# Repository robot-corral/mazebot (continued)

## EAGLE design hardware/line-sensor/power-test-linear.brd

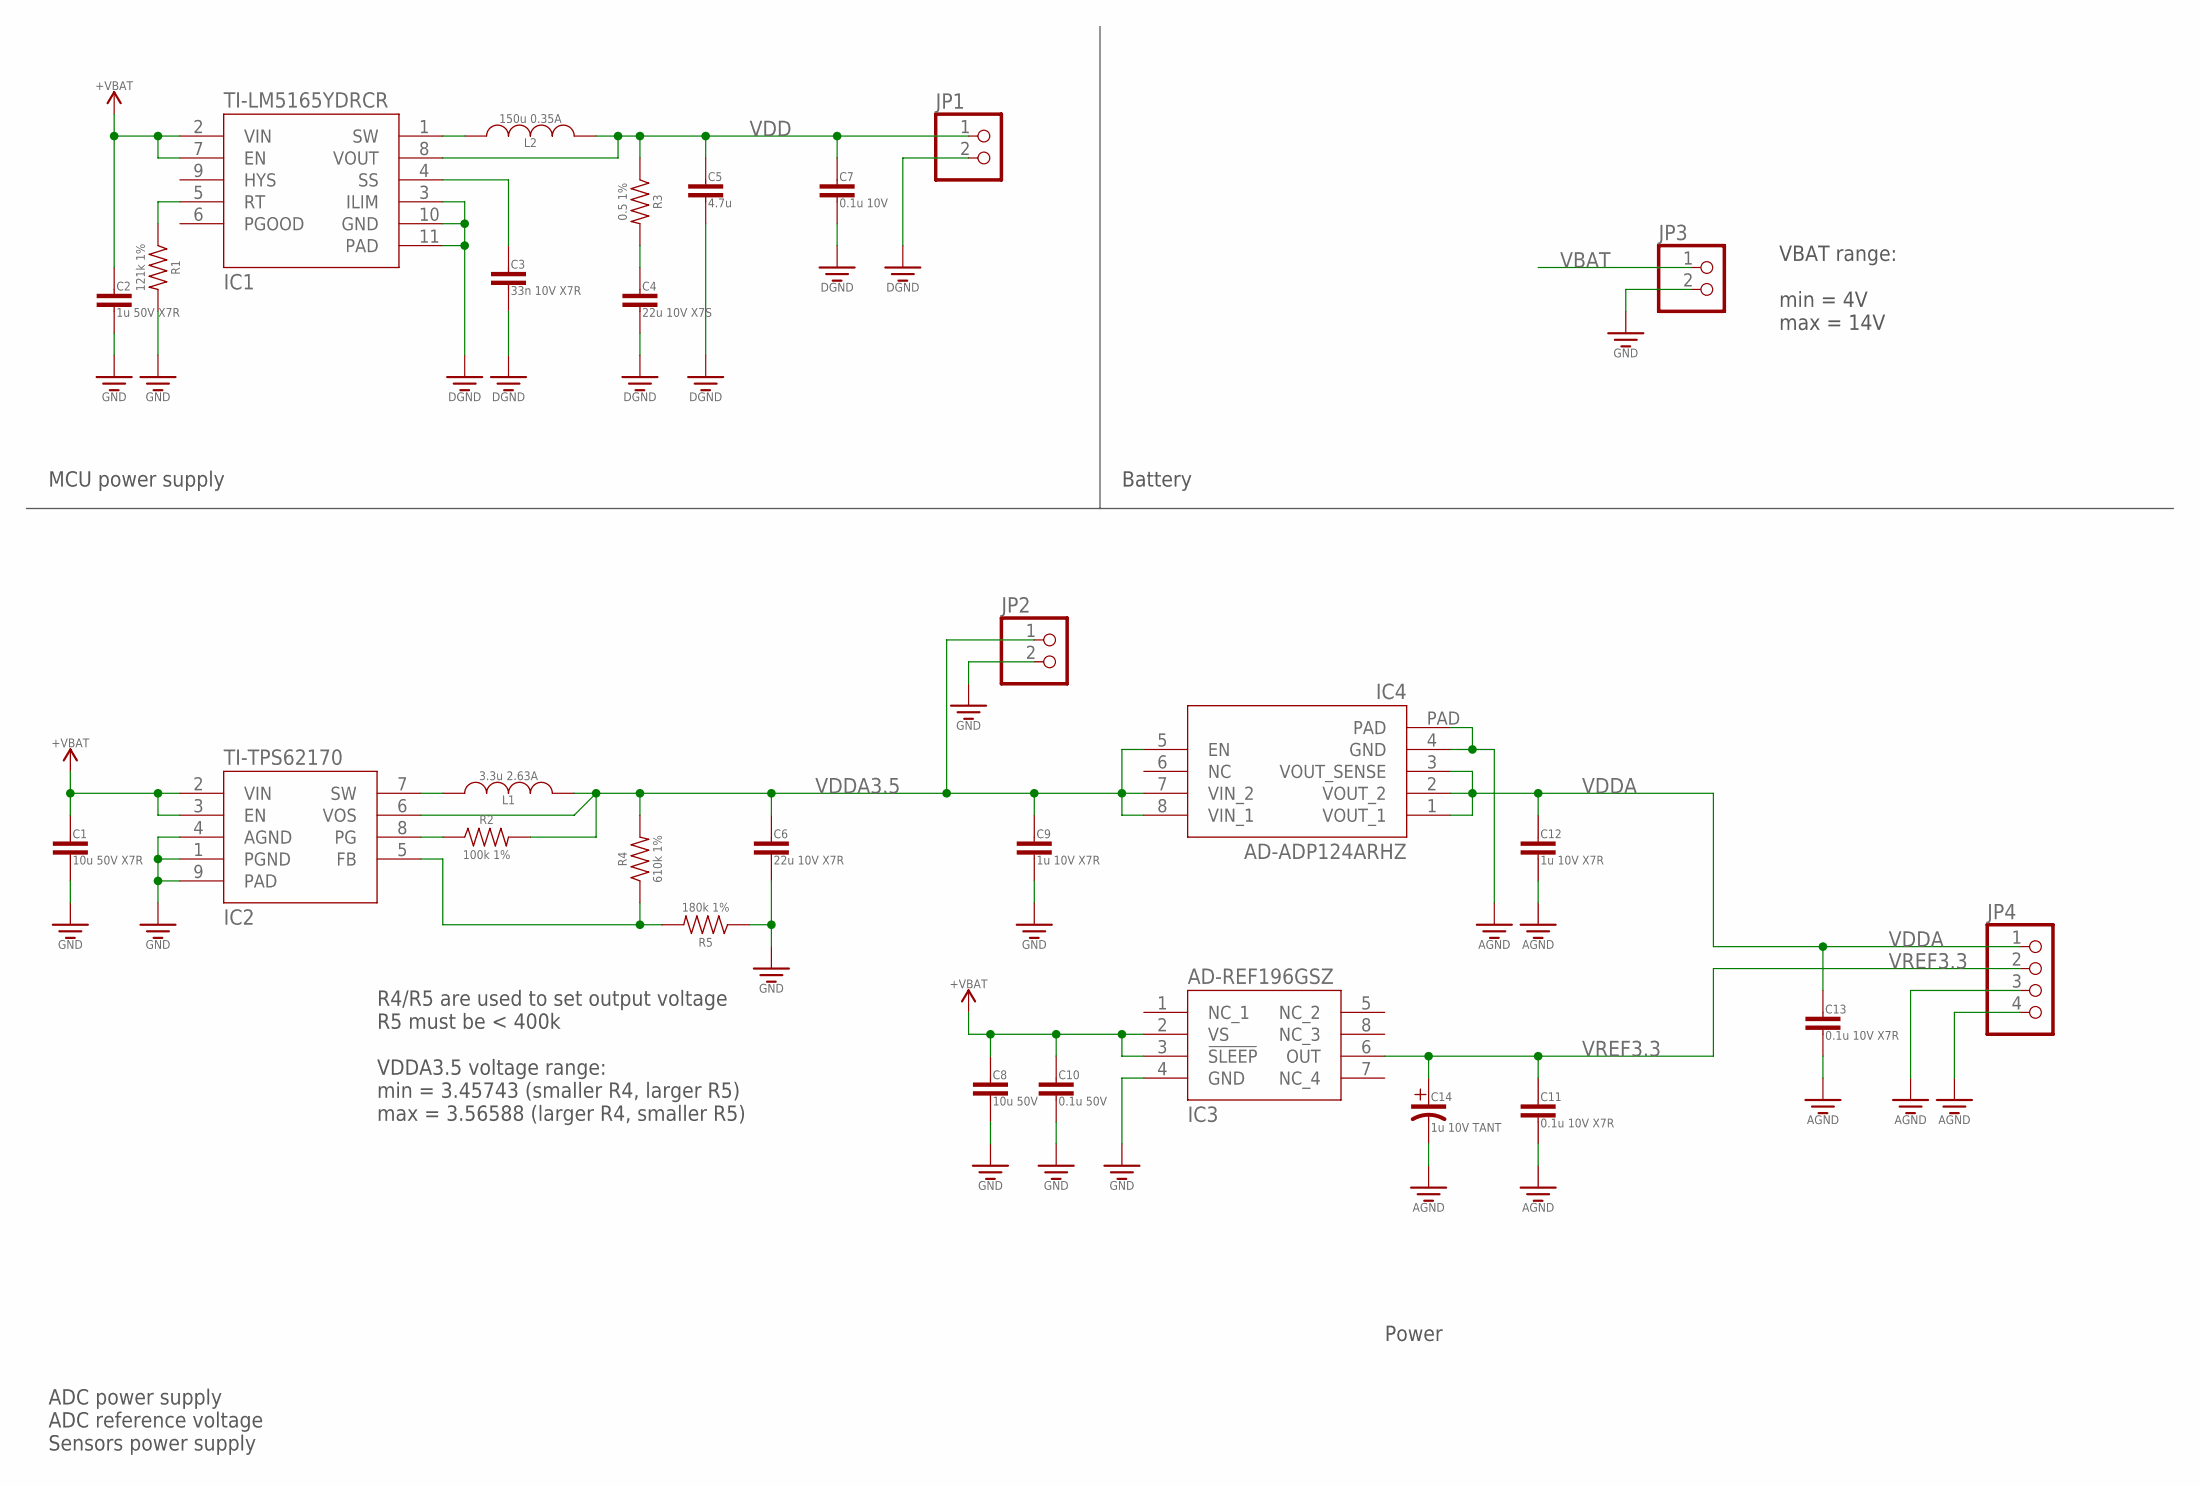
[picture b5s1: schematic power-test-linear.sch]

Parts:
C1: 10u 50V X7R; CAPACITOR-0805
C2: 1u 50V X7R; CAPACITOR-1206
C3: 33n 10V X7R; CAPACITOR-0603
C4: 22u 10V X7S; CAPACITOR-0805
C5: 4.7u; CAPACITOR-0805
C6: 22u 10V X7R; CAPACITOR-0805
C7: 0.1u 10V; CAPACITOR-0805
C8: 10u 50V; CAPACITOR-0805
C9, C12: 1u 10V X7R; CAPACITOR-0805
C10: 0.1u 50V; CAPACITOR-0805
C11, C13: 0.1u 10V X7R; CAPACITOR-0805
C14: 1u 10V TANT; CAPACITOR_POLARIZED-1411-(3528-MET)
IC1: TI-LM5165YDRCR; VSON-10-0.5MM
IC2: TI-TPS62170; WSON-8-0.5MM
IC3: AD-REF196GSZ; SOIC-8
IC4: AD-ADP124ARHZ; MSOP-8-EP
JP1, JP2, JP3: PINHD-1X2; 1X02
JP4: PINHD-1X4; 1X04
L1: 3.3u 2.63A; VLS3012HBX
L2: 150u 0.35A; ELL-6SH151M
R1: 121k 1%; RESISTOR-0603
R2: 100k 1%; RESISTOR-0603
R3: 0.5 1%; RESISTOR-0603
R4: 610k 1%; RESISTOR-0603
R5: 180k 1%; RESISTOR-0603

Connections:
AGND: C11.2, C12.2, C13.2, C14.NEG, IC4.4 (GND), IC4.PAD, JP4.3, JP4.4
DGND: C3.2, C4.2, C5.2, C7.2, IC1.3 (ILIM), IC1.10 (GND), IC1.11 (PAD), JP1.2
GND: C1.2, C2.P$2 (2), C6.2, C8.2, C9.2, C10.2, IC2.1 (PGND), IC2.4 (AGND), IC2.9 (PAD), IC3.4 (GND), JP2.2, JP3.2, R1.P$2 (2), R5.P$1 (1)
unnamed: IC2.7 (SW), L1.1
unnamed: IC2.8 (PG), R2.P$1 (1)
unnamed: C3.1, IC1.4 (SS)
unnamed: IC1.1 (SW), L2.1
unnamed: IC1.5 (RT), R1.P$1 (1)
unnamed: IC2.5 (FB), R4.P$1 (1), R5.P$2 (2)
unnamed: C4.1, R3.P$2 (2)
VBAT: C1.1, C2.P$1 (1), C8.1, C10.1, IC1.2 (VIN), IC1.7 (EN), IC2.2 (VIN), IC2.3 (EN), IC3.2 (VS), IC3.3 (!SLEEP), JP3.1
VDD: C5.1, C7.1, IC1.8 (VOUT), JP1.1, L2.2, R3.P$1 (1)
VDDA: C12.1, C13.1, IC4.1 (VOUT_1), IC4.2 (VOUT_2), IC4.3 (VOUT_SENSE), JP4.1
VDDA3.5: C6.1, C9.1, IC2.6 (VOS), IC4.5 (EN), IC4.7 (VIN_2), IC4.8 (VIN_1), JP2.1, L1.2, R2.P$2 (2), R4.P$2 (2)
VREF3.3: C11.1, C14.POS, IC3.6 (OUT), JP4.2

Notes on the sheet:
Power
MCU power supply
Battery
R4/R5 are used to set output voltage R5 must be < 400k VDDA3.5 voltage range: min = 3.45743 (smaller R4, larger R5) max = 3.56588 (larger R4, smaller R5)
VBAT range: min = 4V max = 14V
ADC power supply ADC reference voltage Sensors power supply

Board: 2 copper layers, 29 parts (0 on the bottom side), 15 nets, no tracks yet.

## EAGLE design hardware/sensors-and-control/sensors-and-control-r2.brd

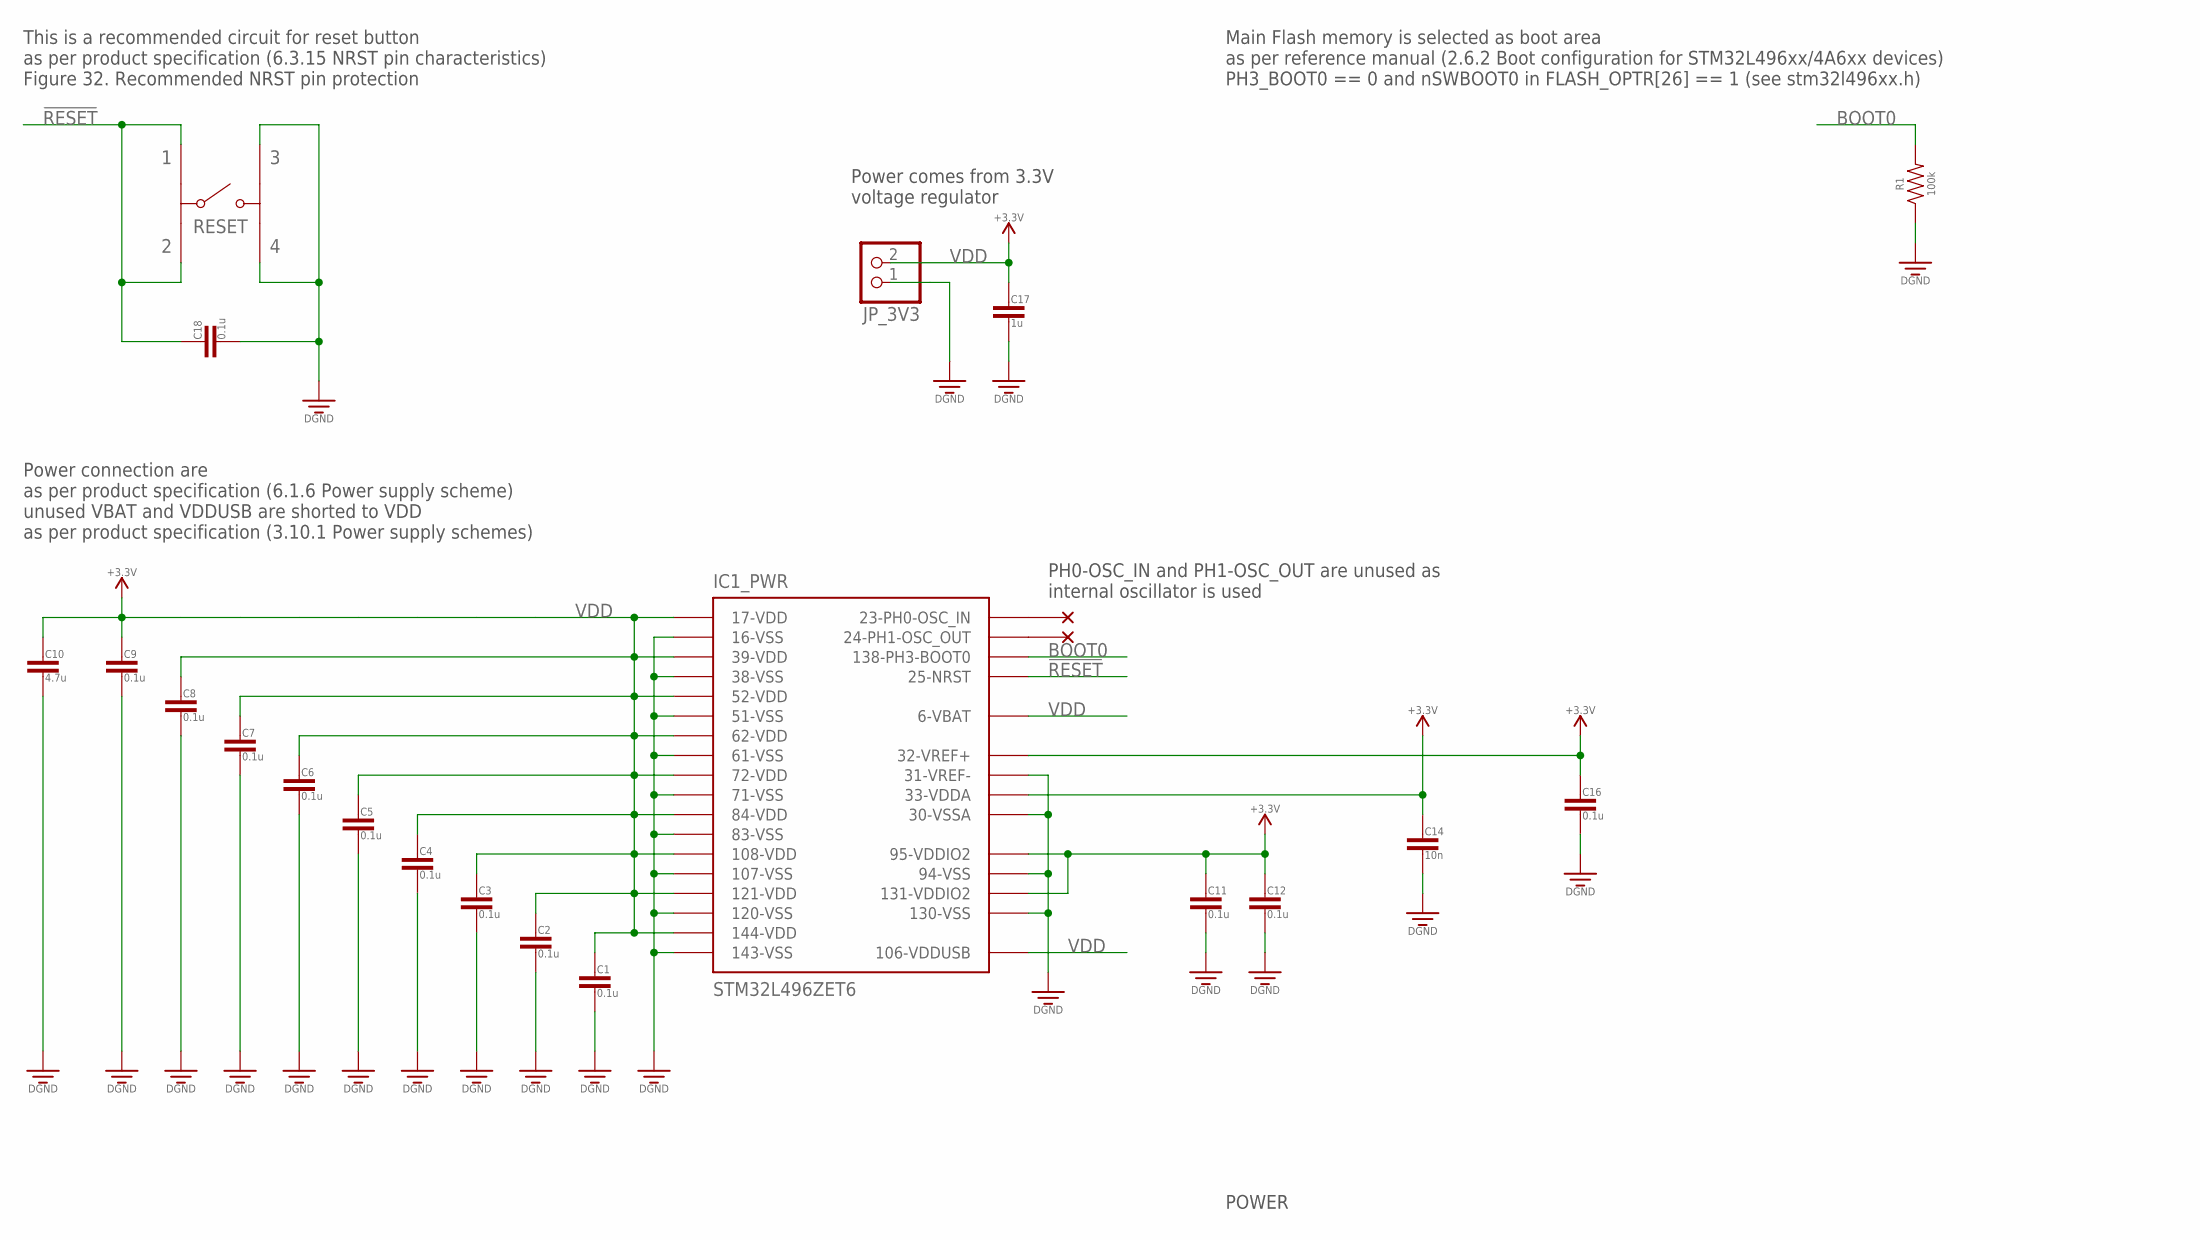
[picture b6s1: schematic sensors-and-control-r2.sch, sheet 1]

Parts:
C1, C2, C3, C4, C5, C6, C7, C8, C9, C11, C12, C16, C18: 0.1u; CAPACITOR-0603
C10: 4.7u; CAPACITOR-0603
C14: 10n; CAPACITOR-0603
C17: 1u; CAPACITOR-0603
IC1: STM32L496ZET6; LQFP144_20X20
JP_3V3: WURTH_691103110002; 2_PINS,3.5MM_PITCH
R1: 100k; RESISTOR-0603
RESET: FSM6JSMAASTR; FSMJSM

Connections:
!RESET: C18.1, IC1.25 (25-NRST), RESET.P$2 (2), RESET.P$4 (1); also elsewhere on the board
BOOT0: IC1.138 (138-PH3-BOOT0), R1.P$2 (2)
DGND: C1.2, C2.2, C3.2, C4.2, C5.2, C6.2, C7.2, C8.2, C9.2, C10.2, C11.2, C12.2, C14.2, C16.2, C17.2, C18.2, IC1.16 (16-VSS), IC1.30 (30-VSSA), IC1.31 (31-VREF-), IC1.38 (38-VSS), IC1.51 (51-VSS), IC1.61 (61-VSS), IC1.71 (71-VSS), IC1.83 (83-VSS), IC1.94 (94-VSS), IC1.107 (107-VSS), IC1.120 (120-VSS), IC1.130 (130-VSS), IC1.143 (143-VSS), JP_3V3.1, R1.P$1 (1), RESET.P$1 (4), RESET.P$3 (3); also elsewhere on the board
VDD: C1.1, C2.1, C3.1, C4.1, C5.1, C6.1, C7.1, C8.1, C9.1, C10.1, C11.1, C12.1, C14.1, C16.1, C17.1, IC1.6 (6-VBAT), IC1.17 (17-VDD), IC1.32 (32-VREF+), IC1.33 (33-VDDA), IC1.39 (39-VDD), IC1.52 (52-VDD), IC1.62 (62-VDD), IC1.72 (72-VDD), IC1.84 (84-VDD), IC1.95 (95-VDDIO2), IC1.106 (106-VDDUSB), IC1.108 (108-VDD), IC1.121 (121-VDD), IC1.131 (131-VDDIO2), IC1.144 (144-VDD), JP_3V3.2; also elsewhere on the board

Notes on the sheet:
Main Flash memory is selected as boot area as per reference manual (2.6.2 Boot configuration for STM32L496xx/4A6xx devices) PH3_BOOT0 == 0 and nSWBOOT0 in FLASH_OPTR[26] == 1 (see stm32l496xx.h)
This is a recommended circuit for reset button as per product specification (6.3.15 NRST pin characteristics) Figure 32. Recommended NRST pin protection
Power connection are as per product specification (6.1.6 Power supply scheme) unused VBAT and VDDUSB are shorted to VDD as per product specification (3.10.1 Power supply schemes)
PH0-OSC_IN and PH1-OSC_OUT are unused as internal oscillator is used
Power comes from 3.3V voltage regulator
POWER

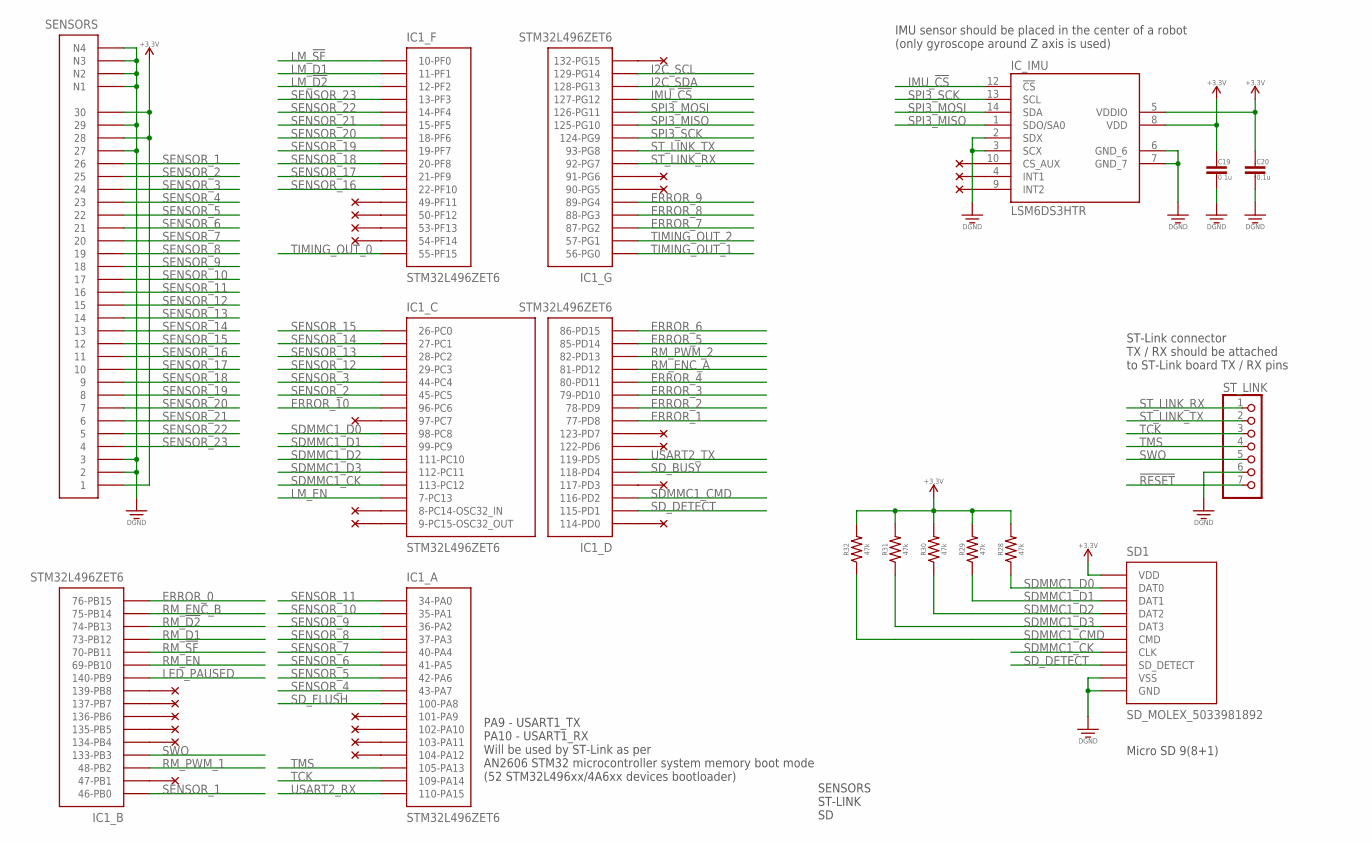
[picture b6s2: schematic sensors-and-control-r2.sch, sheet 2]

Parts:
C19, C20: 0.1u; CAPACITOR-0603
IC1: STM32L496ZET6; LQFP144_20X20
IC_IMU: LSM6DS3HTR; LGA-14L
R28, R29, R30, R31, R32: 47k; RESISTOR-0603
SD1: SD_MOLEX_5033981892
SENSORS: MOLEX-501931-3070
ST_LINK: PINHD-1X7; 1X07

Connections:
!RESET: ST_LINK.7; also elsewhere on the board
DGND: C19.2, C20.2, IC_IMU.2 (SDX), IC_IMU.3 (SCX), IC_IMU.6 (GND_6), IC_IMU.7 (GND_7), SD1.6 (VSS), SD1.DLM (GND), SENSORS.2, SENSORS.3, SENSORS.27, SENSORS.29, SENSORS.NAIL1 (N1), SENSORS.NAIL2 (N2), SENSORS.NAIL3 (N3), SENSORS.NAIL4 (N4), ST_LINK.6; also elsewhere on the board
ERROR_0: IC1.76 (76-PB15); also elsewhere on the board
ERROR_1: IC1.77 (77-PD8); also elsewhere on the board
ERROR_2: IC1.78 (78-PD9); also elsewhere on the board
ERROR_3: IC1.79 (79-PD10); also elsewhere on the board
ERROR_4: IC1.80 (80-PD11); also elsewhere on the board
ERROR_5: IC1.85 (85-PD14); also elsewhere on the board
ERROR_6: IC1.86 (86-PD15); also elsewhere on the board
ERROR_7: IC1.87 (87-PG2); also elsewhere on the board
ERROR_8: IC1.88 (88-PG3); also elsewhere on the board
ERROR_9: IC1.89 (89-PG4); also elsewhere on the board
ERROR_10: IC1.96 (96-PC6); also elsewhere on the board
I2C_SCL: IC1.129 (129-PG14); also elsewhere on the board
I2C_SDA: IC1.128 (128-PG13); also elsewhere on the board
IMU_!CS: IC1.127 (127-PG12), IC_IMU.12 (!CS!)
LED_PAUSED: IC1.140 (140-PB9); also elsewhere on the board
LM_!D2: IC1.12 (12-PF2); also elsewhere on the board
LM_!SF: IC1.10 (10-PF0); also elsewhere on the board
LM_D1: IC1.11 (11-PF1); also elsewhere on the board
LM_EN: IC1.7 (7-PC13); also elsewhere on the board
RM_!D2: IC1.74 (74-PB13); also elsewhere on the board
RM_!SF: IC1.70 (70-PB11); also elsewhere on the board
RM_D1: IC1.73 (73-PB12); also elsewhere on the board
RM_EN: IC1.69 (69-PB10); also elsewhere on the board
RM_ENC_A: IC1.81 (81-PD12); also elsewhere on the board
RM_ENC_B: IC1.75 (75-PB14); also elsewhere on the board
RM_PWM_1: IC1.48 (48-PB2); also elsewhere on the board
RM_PWM_2: IC1.82 (82-PD13); also elsewhere on the board
SDMMC1_CK: IC1.113 (113-PC12), SD1.5 (CLK)
SDMMC1_CMD: IC1.116 (116-PD2), R32.P$1 (1), SD1.3 (CMD)
SDMMC1_D0: IC1.98 (98-PC8), R28.P$1 (1), SD1.7 (DAT0)
SDMMC1_D1: IC1.99 (99-PC9), R29.P$1 (1), SD1.8 (DAT1)
SDMMC1_D2: IC1.111 (111-PC10), R30.P$1 (1), SD1.1 (DAT2)
SDMMC1_D3: IC1.112 (112-PC11), R31.P$1 (1), SD1.2 (DAT3)
SD_BUSY: IC1.118 (118-PD4); also elsewhere on the board
SD_DETECT: IC1.115 (115-PD1), SD1.DSM (SD_DETECT)
SD_FLUSH: IC1.100 (100-PA8); also elsewhere on the board
SENSOR_1: IC1.46 (46-PB0), SENSORS.26
SENSOR_2: IC1.45 (45-PC5), SENSORS.25
SENSOR_3: IC1.44 (44-PC4), SENSORS.24
SENSOR_4: IC1.43 (43-PA7), SENSORS.23
SENSOR_5: IC1.42 (42-PA6), SENSORS.22
SENSOR_6: IC1.41 (41-PA5), SENSORS.21
SENSOR_7: IC1.40 (40-PA4), SENSORS.20
SENSOR_8: IC1.37 (37-PA3), SENSORS.19
SENSOR_9: IC1.36 (36-PA2), SENSORS.18
SENSOR_10: IC1.35 (35-PA1), SENSORS.17
SENSOR_11: IC1.34 (34-PA0), SENSORS.16
SENSOR_12: IC1.29 (29-PC3), SENSORS.15
SENSOR_13: IC1.28 (28-PC2), SENSORS.14
SENSOR_14: IC1.27 (27-PC1), SENSORS.13
SENSOR_15: IC1.26 (26-PC0), SENSORS.12
SENSOR_16: IC1.22 (22-PF10), SENSORS.11
SENSOR_17: IC1.21 (21-PF9), SENSORS.10
SENSOR_18: IC1.20 (20-PF8), SENSORS.9
SENSOR_19: IC1.19 (19-PF7), SENSORS.8
SENSOR_20: IC1.18 (18-PF6), SENSORS.7
SENSOR_21: IC1.15 (15-PF5), SENSORS.6
SENSOR_22: IC1.14 (14-PF4), SENSORS.5
SENSOR_23: IC1.13 (13-PF3), SENSORS.4
SPI3_MISO: IC1.125 (125-PG10), IC_IMU.1 (SDO/SA0)
SPI3_MOSI: IC1.126 (126-PG11), IC_IMU.14 (SDA)
SPI3_SCK: IC1.124 (124-PG9), IC_IMU.13 (SCL)
ST_LINK_RX: IC1.92 (92-PG7), ST_LINK.1
ST_LINK_TX: IC1.93 (93-PG8), ST_LINK.2
SWO: IC1.133 (133-PB3), ST_LINK.5
TCK: IC1.109 (109-PA14), ST_LINK.3
TIMING_OUT_0: IC1.55 (55-PF15); also elsewhere on the board
TIMING_OUT_1: IC1.56 (56-PG0); also elsewhere on the board
TIMING_OUT_2: IC1.57 (57-PG1); also elsewhere on the board
TMS: IC1.105 (105-PA13), ST_LINK.4
USART2_RX: IC1.110 (110-PA15); also elsewhere on the board
USART2_TX: IC1.119 (119-PD5); also elsewhere on the board
VDD: C19.1, C20.1, IC_IMU.5 (VDDIO), IC_IMU.8 (VDD), R28.P$2 (2), R29.P$2 (2), R30.P$2 (2), R31.P$2 (2), R32.P$2 (2), SD1.4 (VDD), SENSORS.1, SENSORS.28, SENSORS.30; also elsewhere on the board

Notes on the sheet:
SENSORS ST-LINK SD
ST-Link connector TX / RX should be attached to ST-Link board TX / RX pins
IMU sensor should be placed in the center of a robot (only gyroscope around Z axis is used)
PA9 - USART1_TX PA10 - USART1_RX Will be used by ST-Link as per AN2606 STM32 microcontroller system memory boot mode (52 STM32L496xx/4A6xx devices bootloader)
Micro SD 9(8+1)

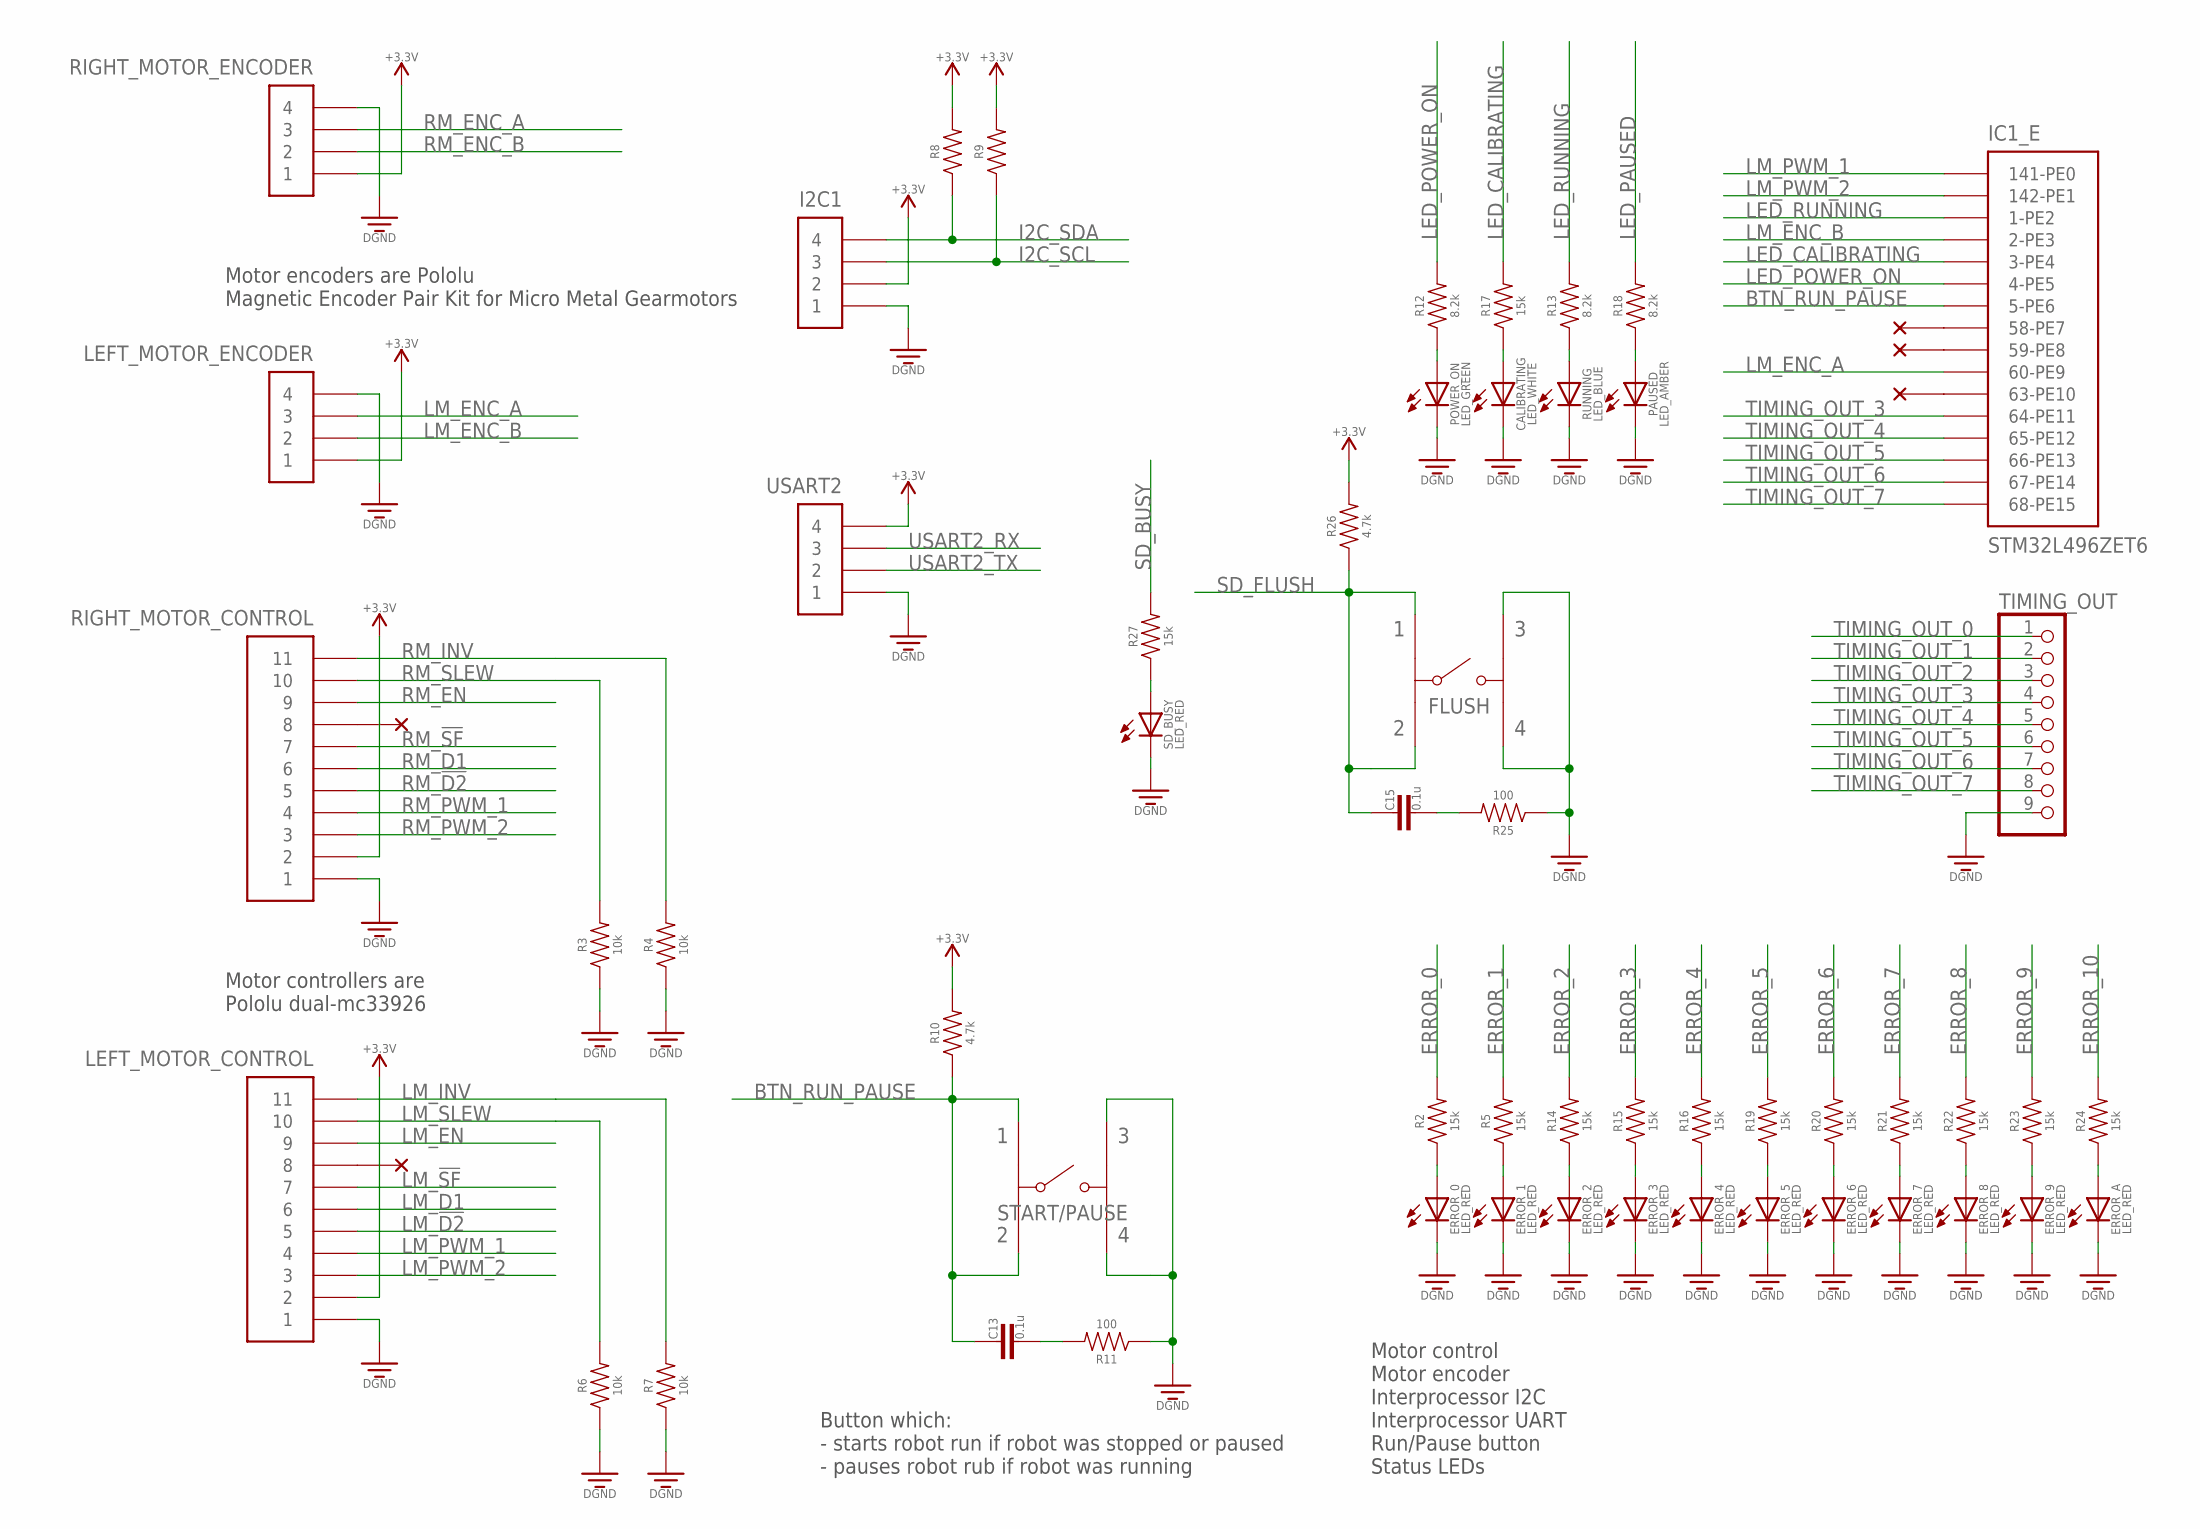
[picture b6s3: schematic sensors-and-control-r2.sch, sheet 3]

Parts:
C13, C15: 0.1u; CAPACITOR-0603
CALIBRATING: LED_WHITE; ESS_II_TYPE_LED
ERROR_0, ERROR_1, ERROR_2, ERROR_3, ERROR_4, ERROR_5, ERROR_6, ERROR_7, ERROR_8, ERROR_9: LED_RED; ESS_II_TYPE_LED
ERROR_A: LED_RED; ESS_II_TYPE_LED
FLUSH: FSM6JSMAASTR; FSMJSM
I2C1: 1X4; MOLEX-70553-0003
IC1: STM32L496ZET6; LQFP144_20X20
LEFT_MOTOR_CONTROL: 1X11; MOLEX-70553-0010
LEFT_MOTOR_ENCODER: 1X4; MOLEX-70553-0003
PAUSED: LED_AMBER; ESS_II_TYPE_LED
POWER_ON: LED_GREEN; ESS_II_TYPE_LED
R2, R5, R14, R15, R16, R17, R19, R20, R21, R22, R23, R24, R27: 15k; RESISTOR-0603
R3, R4, R6, R7: 10k; RESISTOR-0603
R8, R9: RESISTOR_0.1W; RESISTOR-0603
R10, R26: 4.7k; RESISTOR-0603
R11, R25: 100; RESISTOR-0603
R12, R13, R18: 8.2k; RESISTOR-0603
RIGHT_MOTOR_CONTROL: 1X11; MOLEX-70553-0010
RIGHT_MOTOR_ENCODER: 1X4; MOLEX-70553-0003
RUNNING: LED_BLUE; ESS_II_TYPE_LED
SD_BUSY: LED_RED; ESS_II_TYPE_LED
START/PAUSE: FSM6JSMAASTR; FSMJSM
TIMING_OUT: PINHD-1X9; 1X09
USART2: 1X4; MOLEX-70553-0003

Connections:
BTN_RUN_PAUSE: C13.1, IC1.5 (5-PE6), R10.P$1 (1), START/PAUSE.P$2 (2), START/PAUSE.P$4 (1)
DGND: CALIBRATING.P$2 (C), ERROR_0.P$2 (C), ERROR_1.P$2 (C), ERROR_2.P$2 (C), ERROR_3.P$2 (C), ERROR_4.P$2 (C), ERROR_5.P$2 (C), ERROR_6.P$2 (C), ERROR_7.P$2 (C), ERROR_8.P$2 (C), ERROR_9.P$2 (C), ERROR_A.P$2 (C), FLUSH.P$1 (4), FLUSH.P$3 (3), I2C1.1, LEFT_MOTOR_CONTROL.P$1 (1), LEFT_MOTOR_ENCODER.4, PAUSED.P$2 (C), POWER_ON.P$2 (C), R3.P$1 (1), R4.P$1 (1), R6.P$1 (1), R7.P$1 (1), R11.P$1 (1), R25.P$1 (1), RIGHT_MOTOR_CONTROL.P$1 (1), RIGHT_MOTOR_ENCODER.4, RUNNING.P$2 (C), SD_BUSY.P$2 (C), START/PAUSE.P$1 (4), START/PAUSE.P$3 (3), TIMING_OUT.9, USART2.1; also elsewhere on the board
ERROR_0: R2.P$2 (2); also elsewhere on the board
ERROR_1: R5.P$2 (2); also elsewhere on the board
ERROR_2: R14.P$2 (2); also elsewhere on the board
ERROR_3: R15.P$2 (2); also elsewhere on the board
ERROR_4: R16.P$2 (2); also elsewhere on the board
ERROR_5: R19.P$2 (2); also elsewhere on the board
ERROR_6: R20.P$2 (2); also elsewhere on the board
ERROR_7: R21.P$2 (2); also elsewhere on the board
ERROR_8: R22.P$2 (2); also elsewhere on the board
ERROR_9: R23.P$2 (2); also elsewhere on the board
ERROR_10: R24.P$2 (2); also elsewhere on the board
I2C_SCL: I2C1.3, R9.P$1 (1); also elsewhere on the board
I2C_SDA: I2C1.4, R8.P$1 (1); also elsewhere on the board
LED_CALIBRATING: IC1.3 (3-PE4), R17.P$2 (2)
LED_PAUSED: R18.P$2 (2); also elsewhere on the board
LED_POWER_ON: IC1.4 (4-PE5), R12.P$2 (2)
LED_RUNNING: IC1.1 (1-PE2), R13.P$2 (2)
LM_!D2: LEFT_MOTOR_CONTROL.P$5 (5); also elsewhere on the board
LM_!SF: LEFT_MOTOR_CONTROL.P$7 (7); also elsewhere on the board
LM_D1: LEFT_MOTOR_CONTROL.P$6 (6); also elsewhere on the board
LM_EN: LEFT_MOTOR_CONTROL.P$9 (9); also elsewhere on the board
LM_ENC_A: IC1.60 (60-PE9), LEFT_MOTOR_ENCODER.3
LM_ENC_B: IC1.2 (2-PE3), LEFT_MOTOR_ENCODER.2
LM_INV: LEFT_MOTOR_CONTROL.P$11 (11), R7.P$2 (2)
LM_PWM_1: IC1.141 (141-PE0), LEFT_MOTOR_CONTROL.P$4 (4)
LM_PWM_2: IC1.142 (142-PE1), LEFT_MOTOR_CONTROL.P$3 (3)
LM_SLEW: LEFT_MOTOR_CONTROL.P$10 (10), R6.P$2 (2)
unnamed: ERROR_0.P$1 (A), R2.P$1 (1)
unnamed: ERROR_1.P$1 (A), R5.P$1 (1)
unnamed: POWER_ON.P$1 (A), R12.P$1 (1)
unnamed: C13.2, R11.P$2 (2)
unnamed: R13.P$1 (1), RUNNING.P$1 (A)
unnamed: ERROR_2.P$1 (A), R14.P$1 (1)
unnamed: ERROR_3.P$1 (A), R15.P$1 (1)
unnamed: ERROR_4.P$1 (A), R16.P$1 (1)
unnamed: CALIBRATING.P$1 (A), R17.P$1 (1)
unnamed: PAUSED.P$1 (A), R18.P$1 (1)
unnamed: ERROR_5.P$1 (A), R19.P$1 (1)
unnamed: ERROR_6.P$1 (A), R20.P$1 (1)
unnamed: ERROR_7.P$1 (A), R21.P$1 (1)
unnamed: ERROR_8.P$1 (A), R22.P$1 (1)
unnamed: ERROR_9.P$1 (A), R23.P$1 (1)
unnamed: ERROR_A.P$1 (A), R24.P$1 (1)
unnamed: C15.2, R25.P$2 (2)
unnamed: R27.P$1 (1), SD_BUSY.P$1 (A)
RM_!D2: RIGHT_MOTOR_CONTROL.P$5 (5); also elsewhere on the board
RM_!SF: RIGHT_MOTOR_CONTROL.P$7 (7); also elsewhere on the board
RM_D1: RIGHT_MOTOR_CONTROL.P$6 (6); also elsewhere on the board
RM_EN: RIGHT_MOTOR_CONTROL.P$9 (9); also elsewhere on the board
RM_ENC_A: RIGHT_MOTOR_ENCODER.3; also elsewhere on the board
RM_ENC_B: RIGHT_MOTOR_ENCODER.2; also elsewhere on the board
RM_INV: R4.P$2 (2), RIGHT_MOTOR_CONTROL.P$11 (11)
RM_PWM_1: RIGHT_MOTOR_CONTROL.P$4 (4); also elsewhere on the board
RM_PWM_2: RIGHT_MOTOR_CONTROL.P$3 (3); also elsewhere on the board
RM_SLEW: R3.P$2 (2), RIGHT_MOTOR_CONTROL.P$10 (10)
SD_BUSY: R27.P$2 (2); also elsewhere on the board
SD_FLUSH: C15.1, FLUSH.P$2 (2), FLUSH.P$4 (1), R26.P$1 (1); also elsewhere on the board
TIMING_OUT_0: TIMING_OUT.1; also elsewhere on the board
TIMING_OUT_1: TIMING_OUT.2; also elsewhere on the board
TIMING_OUT_2: TIMING_OUT.3; also elsewhere on the board
TIMING_OUT_3: IC1.64 (64-PE11), TIMING_OUT.4
TIMING_OUT_4: IC1.65 (65-PE12), TIMING_OUT.5
TIMING_OUT_5: IC1.66 (66-PE13), TIMING_OUT.6
TIMING_OUT_6: IC1.67 (67-PE14), TIMING_OUT.7
TIMING_OUT_7: IC1.68 (68-PE15), TIMING_OUT.8
USART2_RX: USART2.3; also elsewhere on the board
USART2_TX: USART2.2; also elsewhere on the board
VDD: I2C1.2, LEFT_MOTOR_CONTROL.P$2 (2), LEFT_MOTOR_ENCODER.1, R8.P$2 (2), R9.P$2 (2), R10.P$2 (2), R26.P$2 (2), RIGHT_MOTOR_CONTROL.P$2 (2), RIGHT_MOTOR_ENCODER.1, USART2.4; also elsewhere on the board

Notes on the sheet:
Motor control Motor encoder Interprocessor I2C Interprocessor UART Run/Pause button Status LEDs
Button which: - starts robot run if robot was stopped or paused - pauses robot rub if robot was running
Motor controllers are Pololu dual-mc33926
Motor encoders are Pololu Magnetic Encoder Pair Kit for Micro Metal Gearmotors

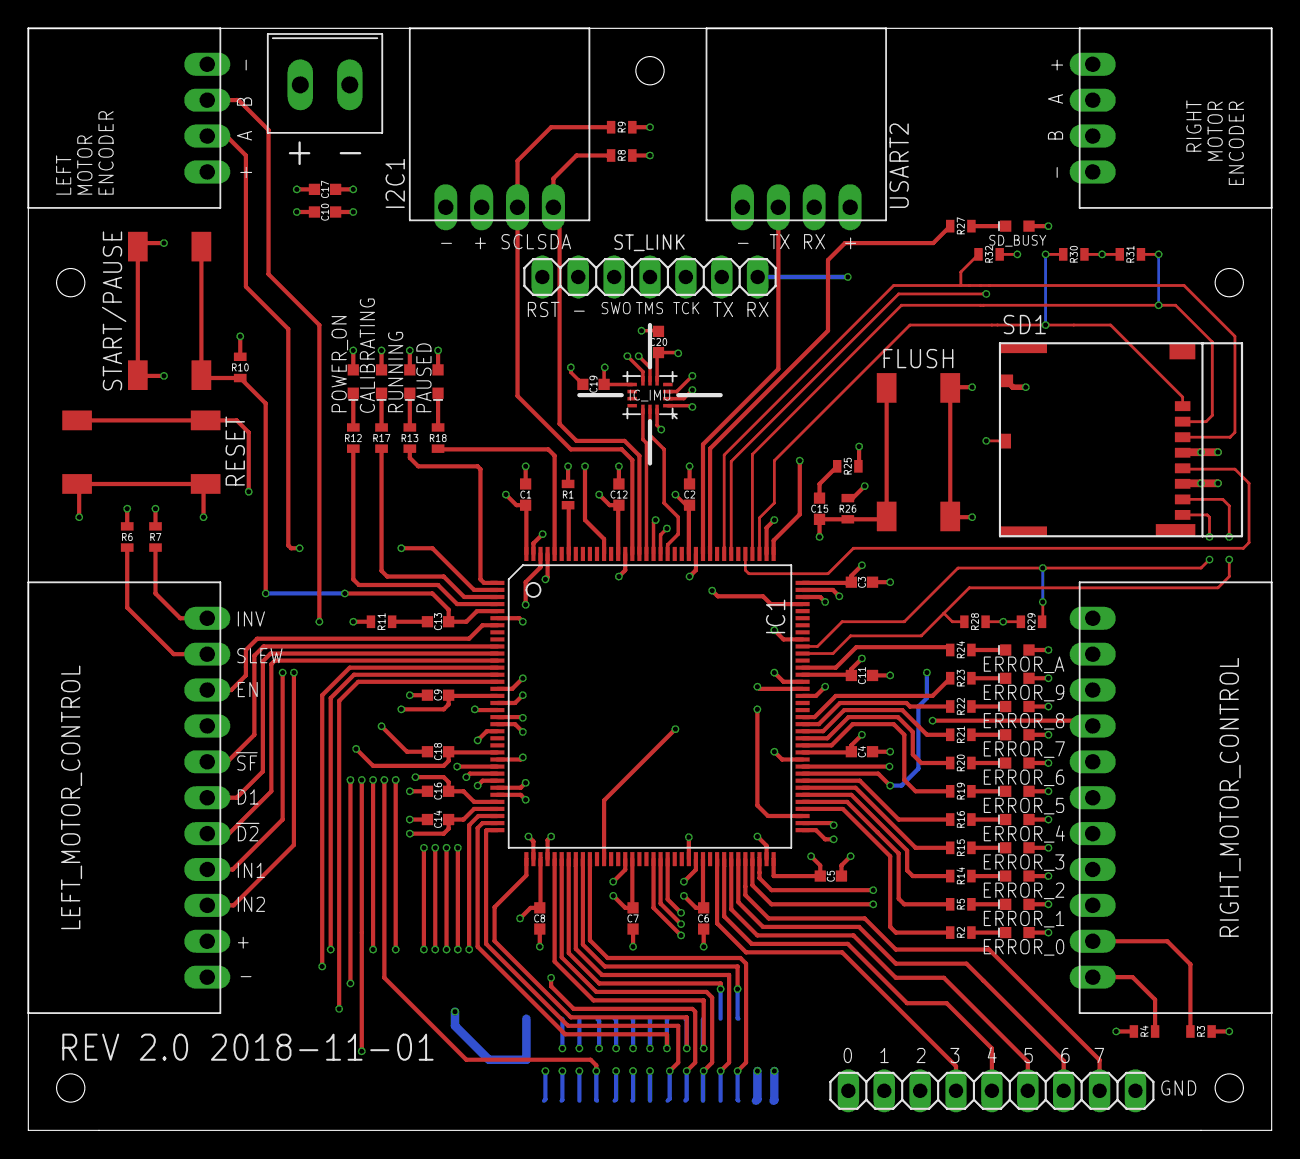
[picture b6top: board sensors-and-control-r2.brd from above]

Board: 4 copper layers, 88.0 x 78.0 mm, 84 parts (1 on the bottom side), 111 nets.
